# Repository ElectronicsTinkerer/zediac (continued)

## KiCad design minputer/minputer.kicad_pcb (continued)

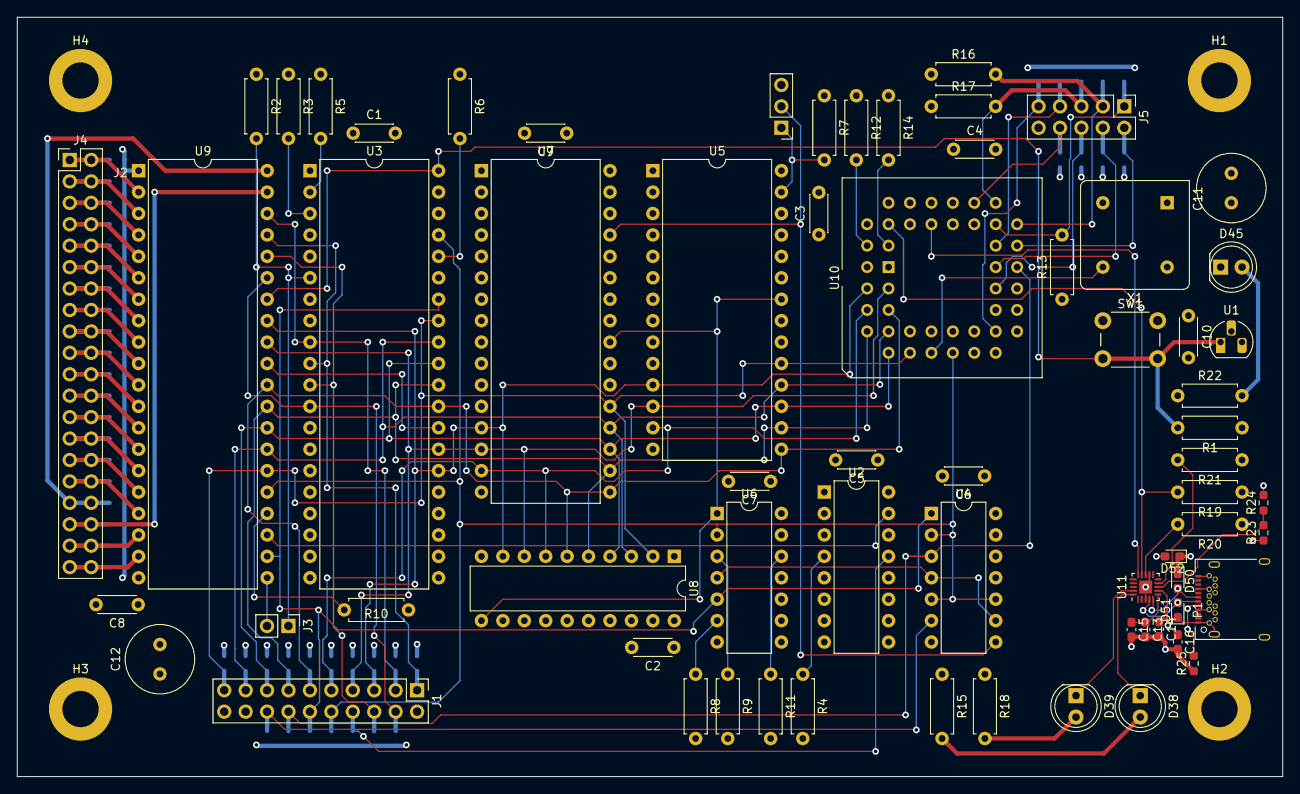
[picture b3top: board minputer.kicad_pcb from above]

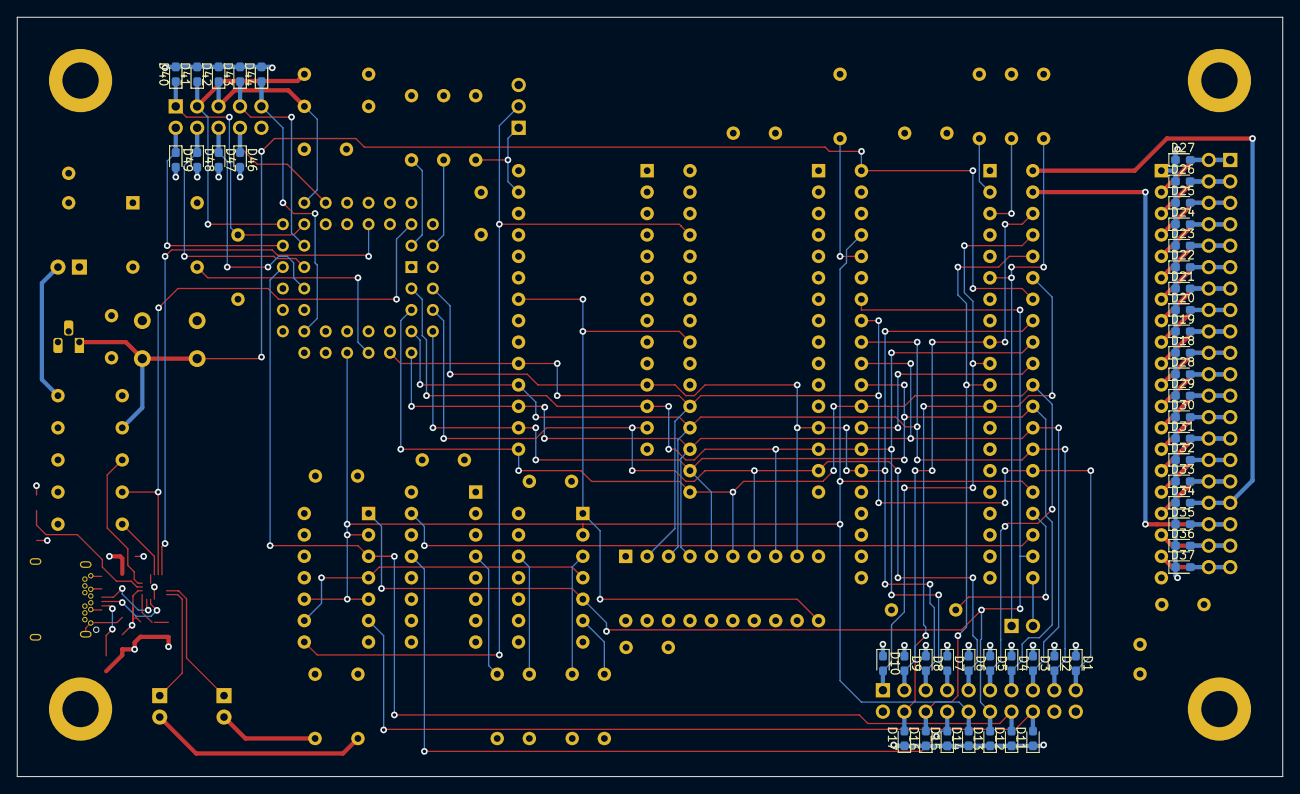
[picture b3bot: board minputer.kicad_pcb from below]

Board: 4 copper layers, 150.0 x 90.0 mm, 116 parts (46 on the bottom side), 107 nets.

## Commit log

2022-10-30 Realize project is not in git; Complete most of schematic
2022-10-31 Finish schematic
2022-10-31 Assign footprints
2022-10-31 Component placement and TVS routing finished
2022-10-31 Remove extra 7400
2022-10-31 Track size change 0.2->0.1524
2022-10-31 Route BUS connector
2022-11-14 Complete initial routing
2022-11-17 Clean up silk screen
2022-12-27 Add aux power input; reroute CP2102; add PHI2 osc
2022-12-27 Add GND TPs; generate logo symbol/model files
2022-12-27 Rename project minputer->zediac
2022-12-27 Add silk labels for connectors and jumpers
2023-01-04 Silk cleanup; add UART INT pulldown resistors
2023-01-04 Correct CP2102 footptint
2023-01-04 Fix reversed databus on '816
2023-01-04 Correct CP2102 power supply
2023-01-04 Change USB footprint
2023-01-05 Change DS1813 footprint
2023-01-05 Export BOM
2023-01-06 Generate gerbers
2023-01-27 Copy in logo files
2023-04-02 Add basic monitor asm file & build script
2023-05-17 Add 6522 and 16C2752 defines; start INIT; add basic sim config
2023-06-04 Finish UART init, implement syscalls for printing
2023-06-04 Fix backspace; fix _sys_puts pointer offset
2023-06-04 Correct dbr value; correct backspace; clear screen on reset
2023-06-05 Implement basic command parser (from EMMA-2)
2023-06-09 Update symbols to make use of the new .def SLIME support
2023-06-11 Correct putdec operation
2023-06-11 Fix 'info' command; fix cli args tokenization and stack set up
2023-06-11 [mon] Correct backspace graphical behavior
2023-06-11 [mon] Rename `info` command to `args`
2023-06-19 [mon] Basic XMODEM recieve implemented
2023-06-20 [mon] Implement go/gosub and SYS_PARX Also: * Improve MONITOR docs (big comment) * Correct SYS_GETCNB p.c return behavior
2023-06-20 [mon] Change SYScalls into enum; Add GETCNB to SYScall list
2023-06-21 [mon] Add memcpy; implement COPY command
2023-06-23 [mon] Prep copy command for EEPROM variant (untested)
2023-06-23 [pcb] Correct PCB design date in SILK
2023-06-25 [mon] Improve COPY command argument checks
2023-06-25 [mon] Complete EEPROM copy command
2023-06-25 [mon] Add hex monitor and start up banner
2023-06-26 [mon] Fix ASCII not printing on some hex dump lines
2023-06-26 [mon] Add newline on ^C to cancel line input
2023-06-27 [mon] Print index across top of hex dump
2023-06-27 [mon] Correct GO/GOSUB command jump indirect (pointer) address
2023-06-29 [mon] XRECV now works (in 816CE)! Key points: * Forgot the ACK after a successful block transfer * Added a flush/purge to the Rx UART FIFO prior to sending NAK * General logic corrections
2023-07-02 [pcb] Correct EEPROM /OE signal; Remove reduandant gate; Bump Rev1.0->1.1
2023-07-02 [docs] Add system photo; create README
2023-07-02 [docs] Introducing the GMLA 4-Clause License, Version 1.0
2023-07-02 [docs] Format LICENSE to 80 cols
2023-07-02 [docs] LICENSE 1.0->1.1, spelling correction
2023-07-05 [mon] XMODEM receive now functions 'properly'
2023-07-05 [mon] Move ASCII buffer for monitor to ZP
2023-07-05 [mon] Add README
2023-07-06 [mon] Change all syscalls to use JSL instead of COP (partially tested)
2023-07-06 [mon] New startup banner idea
2023-07-07 [mon] Limit argc to 100
2023-07-07 [mon] Change startup banner
2023-07-07 [mon] Add memory map command; Change arg delimiter to <' '+1
2023-07-07 [mon] Correct argv stack bug introduced in 4253b3d8
2023-07-07 [mon] Correct argv stack bug
2023-07-07 [mon] Print the parsed command name which is not found
2023-07-07 [mon] Move IRQ/NMI vectors to user-controlled locations
2023-07-07 [mon] Overhaul command table format to allow (reasonably) long commands
2023-07-08 [mon] Add CPU frequency measurement; change getc_to to take arg in seconds
2023-07-08 [mon] Fix crash on XRECV (jsr -> jsl) Also: * Correct cold reset delay arg passing * Fix getc_to delay check ordering This resulted in delays of X-1 instead of X seconds
2023-07-08 [mon] Fix crash on XRECV (jsr -> jsl) Also: * Correct cold reset delay arg passing * Fix getc_to delay check ordering (bug introduced in 426e6bf7) This resulted in delays of X-1 instead of X seconds
2023-07-08 [mon] Fix sys_printdec with single digit numbers
2023-07-08 [mon] Correct 'memmap: command not found'
2023-07-08 [mon] Improve granularity in getc_to; allows faster XMODEM transfers
2023-07-08 [mon] Correct COPY using incorrect bank for SMC
2023-07-08 [mon] Further correct XRECV timing; fix memcpy cound offset
2023-07-09 [mon] Implement (semi-functional) XMODEM send
2023-07-10 [mon] XSEND now functional
2023-07-10 [mon] Fix startup getc timeout by initializing cpu_freq_mhz with dummy value
2023-07-10 [mon] Add MEMSET command
2023-07-12 [mon] Move BRK/COP vectors to user-accessible locations (RAM)
2023-07-12 [docs] Update READMEs to reflect Z/SM v1.7.6
2023-07-13 [mon] Move syscall table to start of ROM; Print return value from GOSUB
2023-07-13 [mon] Make sure we're in native mode on monitor entry
2023-12-08 [lib-curses] Begin basic functions
2023-12-08 [lib-curses] Add basic attrs, movement (untested)
2023-12-09 [lib-curses] Add cur_home function
2023-12-09 [lib-curses] Correct getch A overrite bug
2023-12-09 [app-tracker] Begin UI design for music tracker
2023-12-09 [lib-curses] Don't print leading 0's in movexy
2023-12-09 [mon] Bump UART baud rate (115200 -> 912600)
2023-12-09 [app-tracker] Cursor movement
2023-12-09 [app-tracker] Add note enter functionality
2023-12-09 [mon] Correct puthex_word documentation
2023-12-12 [mon] Add 'load' and 'run' commands
2023-12-24 [pcb] Update to KiCad 7
2023-12-24 [pcb] Add reset jumper/header
2023-12-24 [pcb] Add TVS to reset line
2024-01-06 [lib-curses] Manual loader block
2024-01-06 [app-tracker] Playback? and manual loader blocks; begin SLIME loader testing
2024-01-23 [docs] LICENSE 1.1->1.2, language clarification
2024-03-11 [pcb] Update to KiCad 8
2024-03-11 [exp-template] Create expansion card template
2024-03-11 [pcb] Update (C) date; correct PCB UART silk labels
2024-03-11 [exp-uart] Clone expansion card template
2024-03-13 [exp-uart] Rename files; Insert 4x UART
2024-03-13 [exp-template] Correct template; Create template rename script
2024-03-14 [exp-template] Fix template sch/pcb connection errors
2024-03-15 [exp-uart] Pre-ERC schematic complete
2024-03-15 Update LICENSE copyright year
2024-03-15 [exp-uart] Pass ERC
2024-03-15 [exp-uart] Reannotate & footprint assignment
2024-03-16 [exp-uart] Remove most UART LEDs; Initial pcb placement
2024-03-16 [exp-uart] 90% routed
2024-03-16 [exp-uart] Layout complete; Pass DRC
2024-03-16 [pcb] Export STEP
2024-03-22 [exp-uart] Add board dimensions
2024-03-27 [exp-uart] Add layer indicator
2024-03-27 [exp-uart] Generate Gerbers REV1.0A
